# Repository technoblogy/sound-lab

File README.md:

# Sound Lab
A simple analogue synthesiser consisting of six modules that can be combined in a variety of ways.

For more information see <http://www.technoblogy.com/show?4MGW>.

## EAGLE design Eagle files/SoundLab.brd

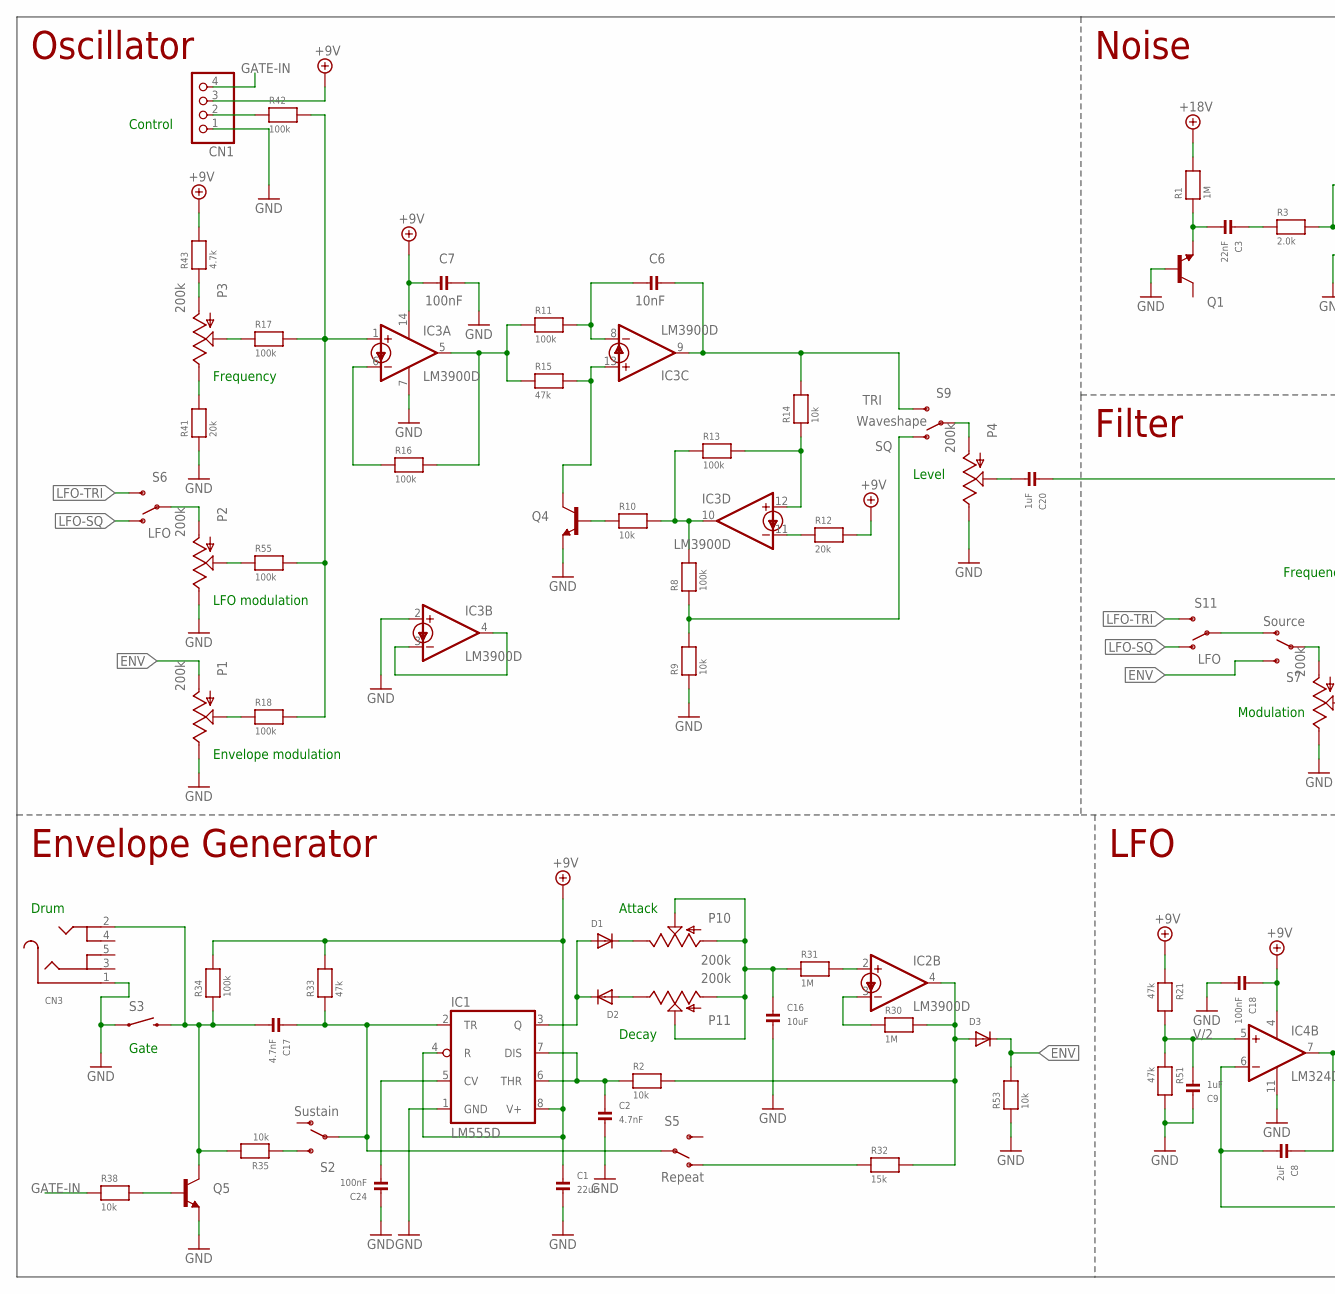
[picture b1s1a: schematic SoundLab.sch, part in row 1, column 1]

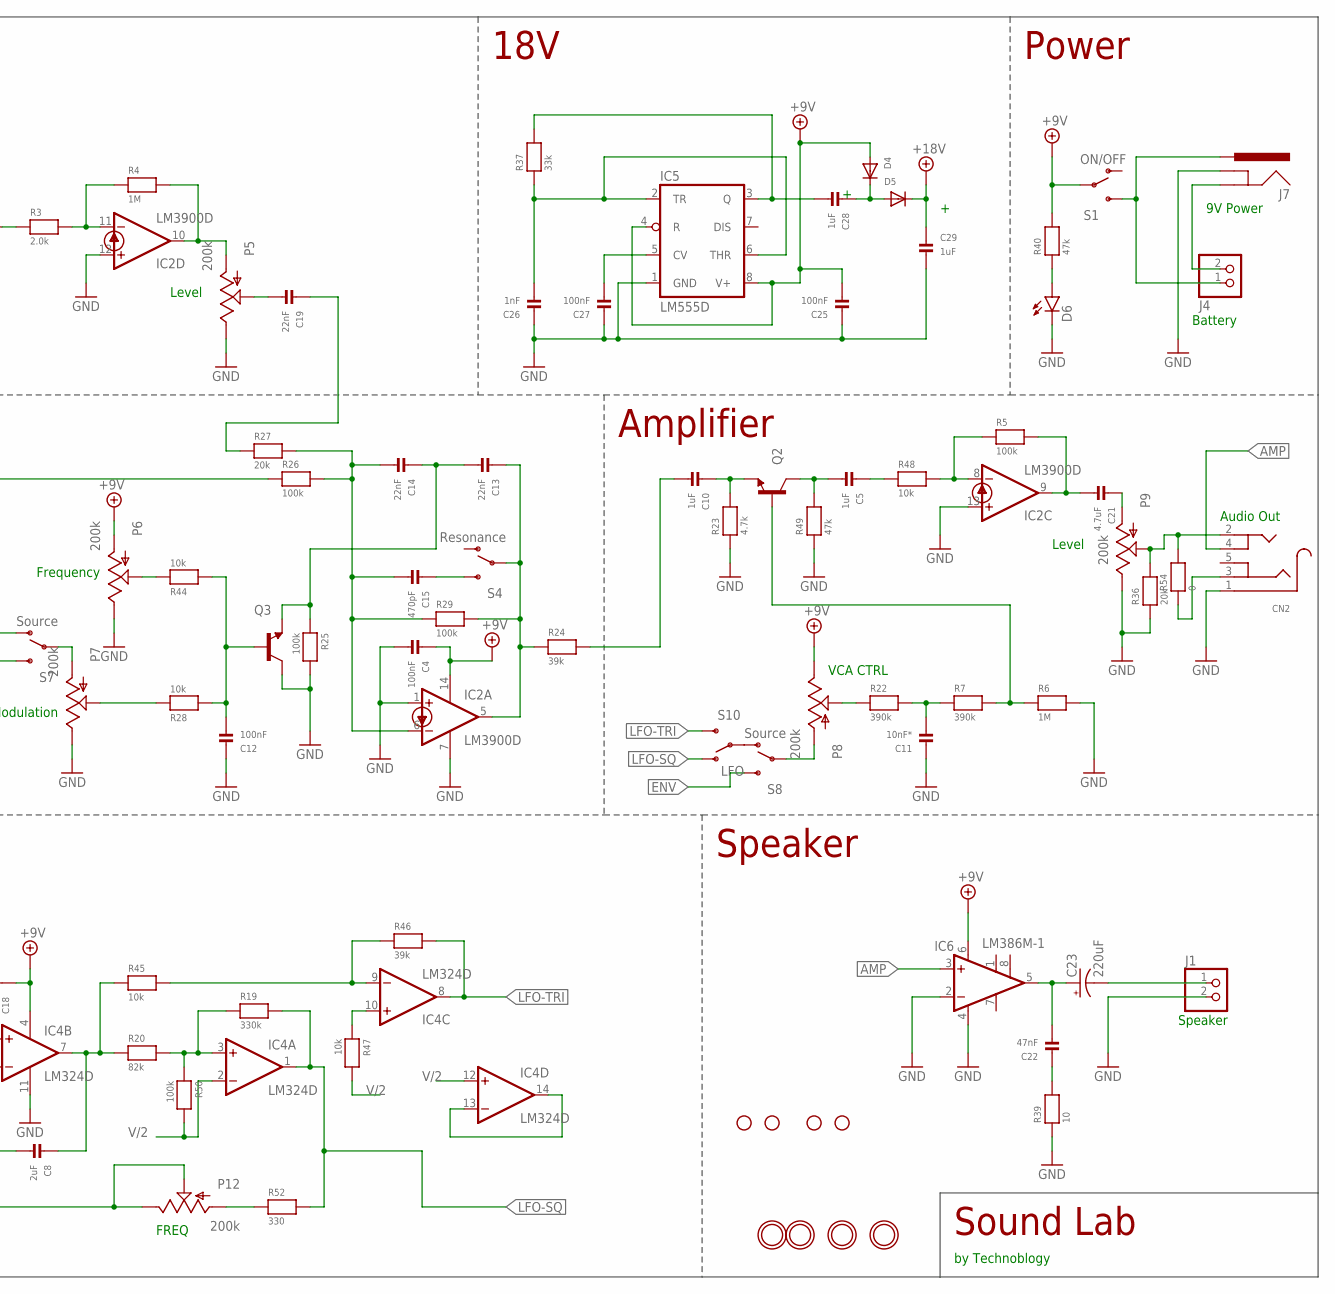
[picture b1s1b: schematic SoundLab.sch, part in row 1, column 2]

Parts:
C1: 22uF; _0805MP
C2, C17: 4.7nF; _0805MP
C3, C13, C14, C19: 22nF; _0805MP
C4, C7, C12, C18, C24, C25, C27: 100nF; _0805MP
C5, C9, C10, C20, C28, C29: 1uF; _0805MP
C6: 10nF; _0805MP
C8: 2uF; _0805MP
C11: 10nF*; _0805MP
C15: 470pF; _0805MP
C16: 10uF; _0805MP
C21: 4.7uF; _0805MP
C22: 47nF; _0805MP
C23: 220uF; PANASONIC_D
C26: 1nF; _0805MP
CN1: JST_4PIN; JSTPH4
CN2, CN3: AUDIO_3.5MMJACK; 4UCONN_19269
D1, D2, D3, D4, D5: DIODESOD-123; SOD-123
D6: LED1206-BOTTOM; LED-1206-BOTTOM
IC1, IC5: LM555D; SO08
IC2, IC3: LM3900D; SO14
IC4: LM324D; SO14
IC6: LM386M-1; SO08
J1, J4: HEADER-1X2EDGE; 1X02_EDGESMT
J7: 5.5x2.1mm Barrel; POWER_JACK_SMD
JP1, JP2, JP3, JP4: STAND-OFF
P1, P2, P3, P4, P5, P6, P7, P8, P9, P10, P11, P12: 200k; ALPS_POT
Q1, Q2, Q3, Q4, Q5: MMBT3904; SOT23-3
R1, R4, R6, R30, R31: 1M; _0805MP
R2, R9, R10, R14, R28, R35, R38, R44, R45, R47, R48, R53: 10k; _0805MP
R3: 2.0k; _0805MP
R5, R8, R11, R13, R16, R17, R18, R25, R26, R29, R34, R42, R50, R55: 100k; _0805MP
R7, R22: 390k; _0805MP
R12, R27, R36, R41: 20k; _0805MP
R15, R21, R33, R40, R49, R51: 47k; _0805MP
R19: 330k; _0805MP
R20: 82k; _0805MP
R23, R43: 4.7k; _0805MP
R24, R46: 39k; _0805MP
R32: 15k; _0805MP
R37: 33k; _0805MP
R39: 10; _0805MP
R52: 330; _0805MP
R54: 0; _0805MP
S1: ON/OFF; SWITCH-SPDT
S2: Sustain; SWITCH-SPDT
S3: SWITCH-MOMENTARY-212MM; TACTILE-PTH-12MM
S4: Resonance; SWITCH-SPDT
S5: Repeat; SWITCH-SPDT
S6, S10, S11: LFO; SWITCH-SPDT
S7, S8: Source; SWITCH-SPDT
S9: Waveshape; SWITCH-SPDT
U$2, U$3, U$6, U$7: MOUNTINGHOLE2.0; MOUNTINGHOLE_2.0_PLATED

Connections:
+9V: C1.1, C4.1, C7.2, C18.1, C25.2, CN1.3, D4.A, IC1.4 (R), IC1.8 (V+), IC2.14 (V+), IC3.14 (V+), IC4.4 (V+), IC5.4 (R), IC5.8 (V+), IC6.6 (VS), P6.P$3 (A), P8.P$1 (E), R12.2, R21.1, R33.2, R34.2, R40.2, R43.2, S1.2
+18V: C29.1, D5.C, R1.2
AMP: CN2.4, IC6.3 (+IN)
ENV: D3.C, P1.P$3 (A), R53.2, S7.3 (S), S8.3 (S)
ENV2: D3.A, IC2.4 (OUT), R2.2, R30.2, R32.2
GATE-IN: CN1.4, R38.1
GND: C1.2, C2.2, C4.2, C7.1, C9.1, C11.1, C12.1, C16.2, C18.2, C24.1, C25.1, C26.1, C27.1, C29.2, CN1.1, CN2.1, CN3.1, D6.C, IC1.1 (GND), IC2.1 (+IN), IC2.7 (GND), IC2.12 (+IN), IC2.13 (+IN), IC3.2 (+IN), IC3.7 (GND), IC4.11 (V-), IC5.1 (GND), IC6.2 (-IN), IC6.4 (GND), J1.2, J7.GND (GNDBREAK), P1.P$1 (E), P2.P$1 (E), P4.P$1 (E), P5.P$1 (E), P6.P$1 (E), P7.P$1 (E), P9.P$1 (E), Q1.1 (B), Q3.3 (C), Q4.2 (E), Q5.2 (E), R6.2, R9.1, R23.1, R25.2, R36.1, R39.1, R41.1, R49.1, R51.2, R53.1, S3.1
LFO->VCA: S8.1 (O), S10.2
LFO->VCF: S7.1 (O), S11.2
LFO->VCO: P2.P$3 (A), S6.2
LFO-SQ: IC4.1 (OUT), R19.2, R52.2, S6.1 (O), S10.1 (O), S11.1 (O)
LFO-TRI: IC4.8 (OUT), R46.2, S6.3 (S), S10.3 (S), S11.3 (S)
unnamed: IC3.1 (+IN), R17.2, R18.2, R42.2, R55.2
unnamed: IC3.6 (-IN), R16.1
unnamed: IC3.5 (OUT), R11.1, R15.1, R16.2
unnamed: IC3.13 (+IN), Q4.3 (C), R15.2
unnamed: C6.2, IC3.8 (-IN), R11.2
unnamed: C8.1, IC4.7 (OUT), R20.1, R45.1
unnamed: Q4.1 (B), R10.1
unnamed: IC3.10 (OUT), R8.2, R10.2, R13.1
unnamed: R32.1, S5.1 (O)
unnamed: C17.1, IC1.2 (TR), R33.1, S2.2, S5.2
unnamed: C19.1, R27.1
unnamed: C21.2, IC2.9 (OUT), R5.2
unnamed: C2.1, IC1.6 (THR), IC1.7 (DIS), R2.1
unnamed: P2.P$2 (S), R55.1
unnamed: IC4.3 (+IN), R19.1, R20.2, R50.1
unnamed: P7.P$2 (S), R28.1
unnamed: Q5.1 (B), R38.2
unnamed: CN2.3, R54.1
unnamed: C16.1, P10.P$2 (S), P10.P$3 (A), P11.P$2 (S), P11.P$3 (A), R31.1
unnamed: CN1.2, R42.1
unnamed: D2.A, P11.P$1 (E)
unnamed: D1.A, D2.C, IC1.3 (Q)
unnamed: P6.P$2 (S), R44.1
unnamed: IC3.11 (-IN), R12.1
unnamed: C10.2, R24.2
unnamed: C5.2, Q2.3 (C), R49.2
unnamed: P3.P$3 (A), R43.1
unnamed: C10.1, Q2.2 (E), R23.2
unnamed: P3.P$1 (E), R41.2
unnamed: P3.P$2 (S), R17.1
unnamed: P1.P$2 (S), R18.1
unnamed: IC2.8 (-IN), R5.1, R48.2
unnamed: IC3.12 (+IN), R13.2, R14.1
unnamed: C8.2, IC4.6 (-IN), P12.P$1 (E), P12.P$2 (S)
unnamed: R35.1, S2.3 (S)
unnamed: C5.1, R48.1
unnamed: IC4.13 (-IN), IC4.14 (OUT)
unnamed: C23.-, J1.1
unnamed: P12.P$3 (A), R52.1
unnamed: IC2.2 (+IN), R31.2
unnamed: CN2.2, P9.P$2 (S), R36.2, R54.2
unnamed: IC4.9 (-IN), R45.2, R46.1
unnamed: J4.2, J7.P$4 (GND)
unnamed: P8.P$2 (S), R22.1
unnamed: IC4.10 (+IN), R47.1
unnamed: C3.1, R3.1
unnamed: IC2.11 (-IN), R3.2, R4.1
unnamed: IC2.10 (OUT), P5.P$3 (A), R4.2
unnamed: C3.2, Q1.2 (E), R1.1
unnamed: C20.2, P4.P$2 (S)
unnamed: C21.1, P9.P$3 (A)
unnamed: C19.2, P5.P$2 (S)
unnamed: C13.2, C14.1, Q3.2 (E), R25.1
unnamed: D1.C, P10.P$1 (E)
unnamed: P7.P$3 (A), S7.2
unnamed: C13.1, IC2.5 (OUT), R24.1, R29.2, S4.2
unnamed: D6.A, R40.1
unnamed: C12.2, Q3.1 (B), R28.2, R44.2
unnamed: C15.1, S4.3 (S)
unnamed: C22.2, C23.+, IC6.5 (OUT)
unnamed: P8.P$3 (A), S8.2
unnamed: C17.2, CN3.2, Q5.3 (C), R34.1, R35.2, S3.3 (2)
unnamed: C11.2, R7.1, R22.2
unnamed: Q2.1 (B), R6.1, R7.2
unnamed: IC3.3 (-IN), IC3.4 (OUT)
unnamed: C28.2, IC5.3 (Q), R37.2
unnamed: C26.2, IC5.2 (TR), IC5.6 (THR), R37.1
unnamed: IC2.3 (-IN), R30.1
unnamed: C27.2, IC5.5 (CV)
unnamed: C28.1, D4.C, D5.A
unnamed: C24.2, IC1.5 (CV)
unnamed: C22.1, R39.2
unnamed: J4.1, J7.VIN0 (PWR), S1.3 (S)
NOISE: C14.2, C15.2, IC2.6 (-IN), R26.2, R27.2, R29.1
SQ: R8.1, R9.2, S9.1 (O)
TRI: C6.1, IC3.9 (OUT), R14.2, S9.3 (S)
V/2: C9.2, IC4.2 (-IN), IC4.5 (+IN), IC4.12 (+IN), R21.2, R47.2, R50.2, R51.1
WAVE: P4.P$3 (A), S9.2
WAVEFORM: C20.1, R26.1

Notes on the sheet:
Frequency
Oscillator
Envelope modulation
Level
Attack
Envelope Generator
LFO
Noise
Filter
Gate
FREQ
Decay
Modulation
Amplifier
Speaker
18V
Power
Battery
VCA CTRL
Drum
LFO modulation
Control
9V Power
Sound Lab
Audio Out
by Technoblogy

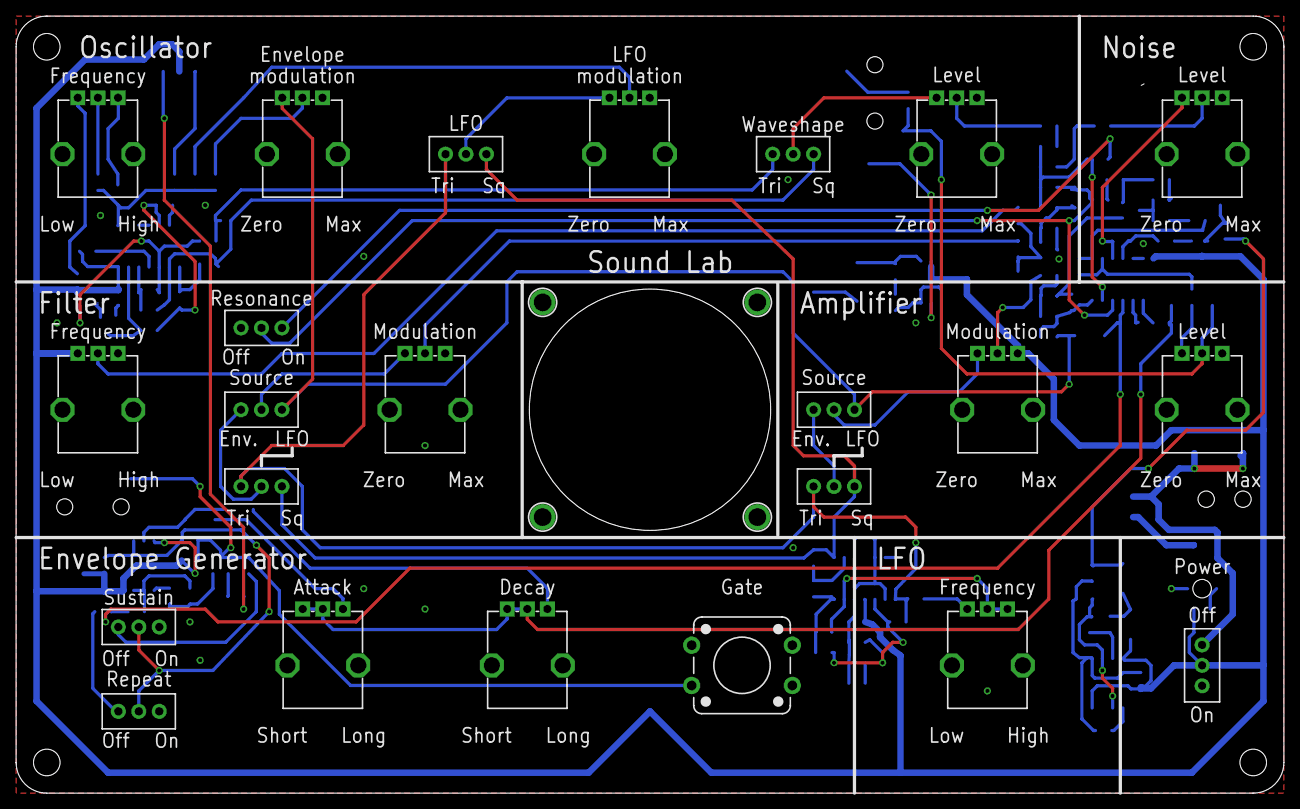
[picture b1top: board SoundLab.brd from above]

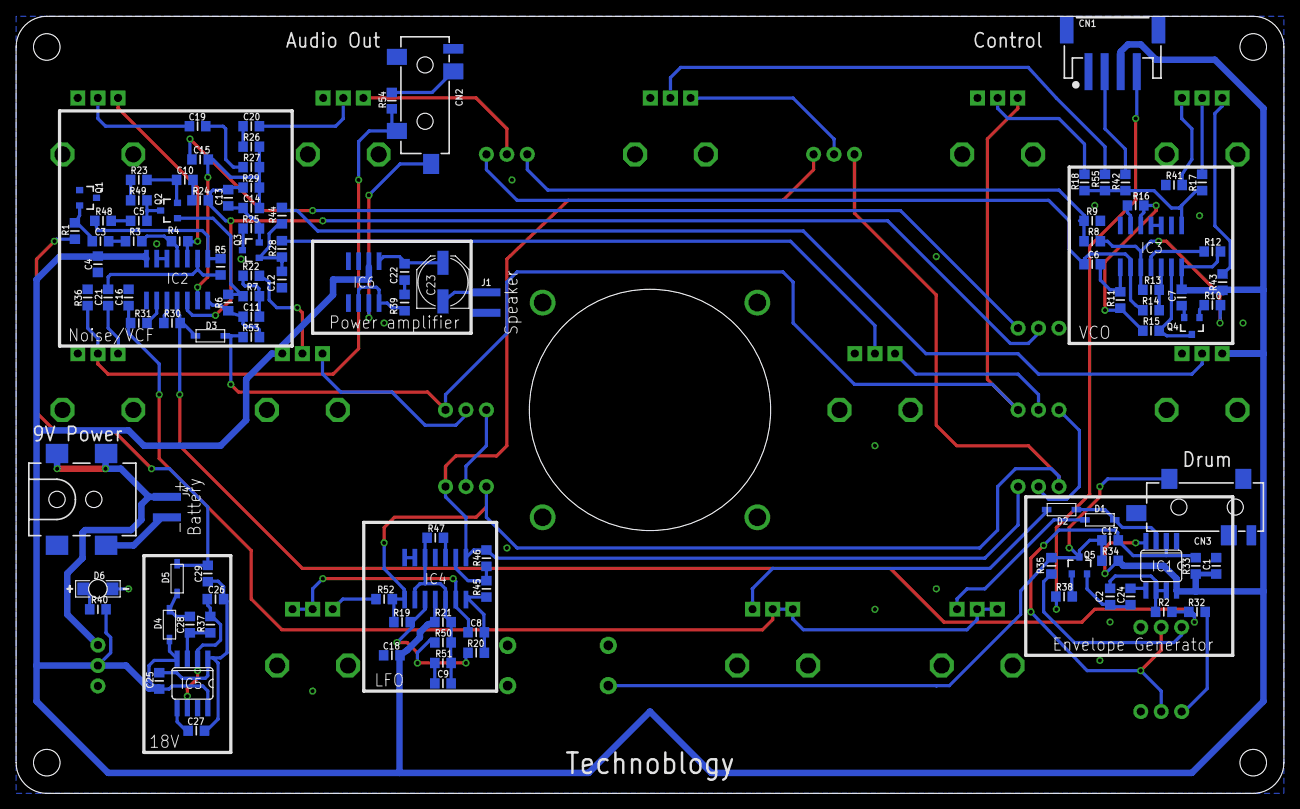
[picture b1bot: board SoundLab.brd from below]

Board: 2 copper layers, 157.5 x 96.5 mm, 138 parts (107 on the bottom side), 91 nets.

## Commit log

2024-05-30 Version 1 - 30th May 2024
2024-11-12 R100->R55

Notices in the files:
parts and their libraries:
SparkFun-Electromechanical: Licensing: Creative Commons ShareAlike 4.0 International - https://creativecommons.org/licenses/by-sa/4.0
microbuilder: This work is placed in the public domain, and may be freely used for commercial and non-commercial work with the following conditions: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
